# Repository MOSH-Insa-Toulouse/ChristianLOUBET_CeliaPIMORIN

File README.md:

# Projet_MOSH 

# 1. Introduction

Le 25 janvier 2021, nous avons commencé le projet «du capteur au banc de test en open source hardware», ce projet a pour but de vérifier la viabilité de la technologie des capteurs électronique à base de papier. Les capteurs à base papier peuvent être utilisé comme jauges de contrainte pour détecter les déformations: de compression et de traction. Ces capteurs peuvent être fabriqué sans électrodes métalliques en utilisant seulement le graphite issu des crayons à papier. Afin de tester nos capteurs nous avons réalisé notre banc de test et nous exploitons nos capteurs avec un circuit imprimé connecté à une Shield Arduino, ce montage transmet par Bluetooth nos mesures vers l’application APK, nous utilisons cette application sur nos smartphones. 

# 2. Capteur Graphite

La résistance du capteur graphite: Sur le papier est déposé du graphite, des atomes de carbones sont donc à la surface du papier, il y a une distance a entre chacun des atomes. Quand le capteur subit une déformation, sa longueur L s’agrandit/diminue et il en va de même pour la distance a entre les atomes. La déformation du capteur papier fait varier la résistance du capteur, car la longueur du capteur et la distance entre les atomes varie elle aussi. La sensibilité du capteur est très grande car elle dépend de l'effet tunnel qui dépend exponentiellement de la ditance entre le particules. Nos capteurs papier ont une zone nominale d’emploi, il ne faut pas trop déformer les capteurs(la déformation ne doit dépasser les 1 %).Les mines de crayon les plus dures(9H, 7H, 5H...) contiennent une proportion plus élevée de colle argileuse tandis que les mines les plus molles (5B,7B, 9B...) ont une proportion de particules de graphite, moins il y a de graphite sur le papier et plus la résistance du capteur augmente. 

Le principe physique du capteur repose sur les systèmes granulaires. Un système granulaire est un système avec des grains de tailles nanométrique où la conductance intragrain est très grande devant la conductance intergrain. En effet la conductance inter grain est la conductance entre deux particules et la conductance intragrain dépend de la diffusivité de la particule quantique qui depend de l'espacement entre les niveaux d'énergie. 
La conductance dans un système granulaire dépend de la constante de barrière tunnel, l'interdistance, l'energie de chargement et de la température.

# 3. Code Arduino
Quand nous connectons notre circuit imprimé avec le Shield Arduino, les pin Rx et Tx du circuit sont connectés aux ports 10 et 11 du Shield. En fait, les port 0 et 1 du Shield sont automatiquement reconfigurés : pin 0 et pin1 deviennent Rx et Tx, il devient donc impossible d’utiliser ces 2 ports, les port 10 et 11 sont donc redéfinies sur le code pour pouvoir transmettre les informations par le module HC-05.
Nous avons codé plusieurs fonctions sur Arduino, la première permet de transmettre par Bluetooth la valeur de la tension aux bornes du capteur papier, la tension est codée en binaire et envoyée par paquet de 10 bit, la seconde fonction affiche les valeurs de la tension (mesuré en Volt, il y a une conversion qui est faite dans le code) et la valeur de la résistance (en Ohm) sur l’écran OLED, Il faut noter que les mesures sont prises toutes les 20 millisecondes. 

# 4. Code APK
Sur ce code APK, nous avons organisé la face avant avec un canvas pour représenter graphiquement la résistance du capteur en temps réel, nous pouvons nous connecter par Bluetooth en sélectionnant les appareils détectables par le smartphone. Notre code traite les données envoyées par Bluetooth, il calcule la valeur de la résistance.

# 5. La Shield
Nous avons pu souder notre circuit imprimé sans court-circuit, nous avons soudé 4 ports femelles supplémentaires : 2 pour connecter les pinces qui sont reliées au capteur papier et 2 autres afin de changer plus facilement la résistance R2, cette résistance fait varier la valeur du gain d’amplification, notre Shield Arduino est alimentée sous 5 Volt, mais en fonction de la quantité de graphite déposée sur le capteur et de la valeur de R2, notre signal peut saturer à 5 Volt ou bien être tellement faible qu’il n’ai pas détectable. 
Enfin, nous avons des ports pour connecter l’écran OLED, l’encodeur rotatoire et le module Bluetooth.

Sur KiCad, nous avons créé des emplacements pour les connecteurs du module HC-05, de l’écran OLED, de l’encodeur rotatoire, de l’amplificateur et le capteur papier. Sur la schématique, nous avons dessiné le montage transimpédance (Filtre passe-bas + montage amplificateur)
Nous avons routé les différents emplacements entre eux, toutes les masses sont reliée par un plan de masse. 

# 6. Le Protocol pour le banc de test

Au début nous déformions notre capteur avec un banc de test cylindrique mais nous avions des mesures aberrantes, c’est en montrant nos résultats à notre professeur que nous avons compris l’origine du problème: les rayons de courbure du cylindre sont trop grands et cela fait dépasser la zone nominale d’emploi de nos capteurs. Sur conseil de Monsieur Grisolia, nous avons utilisé un autre banc de test: avec du ruban adhésif, nous fixons les pinces du capteur sur le bord d’une table, nous mettions une règle sous l’extrémité du capteur qui dépasse de la table. Avec la règle nous déformions le capteur, nous la faisions glisser très légèrement vers le haut. Cela permet de mieux contrôler la déformation du capteur.

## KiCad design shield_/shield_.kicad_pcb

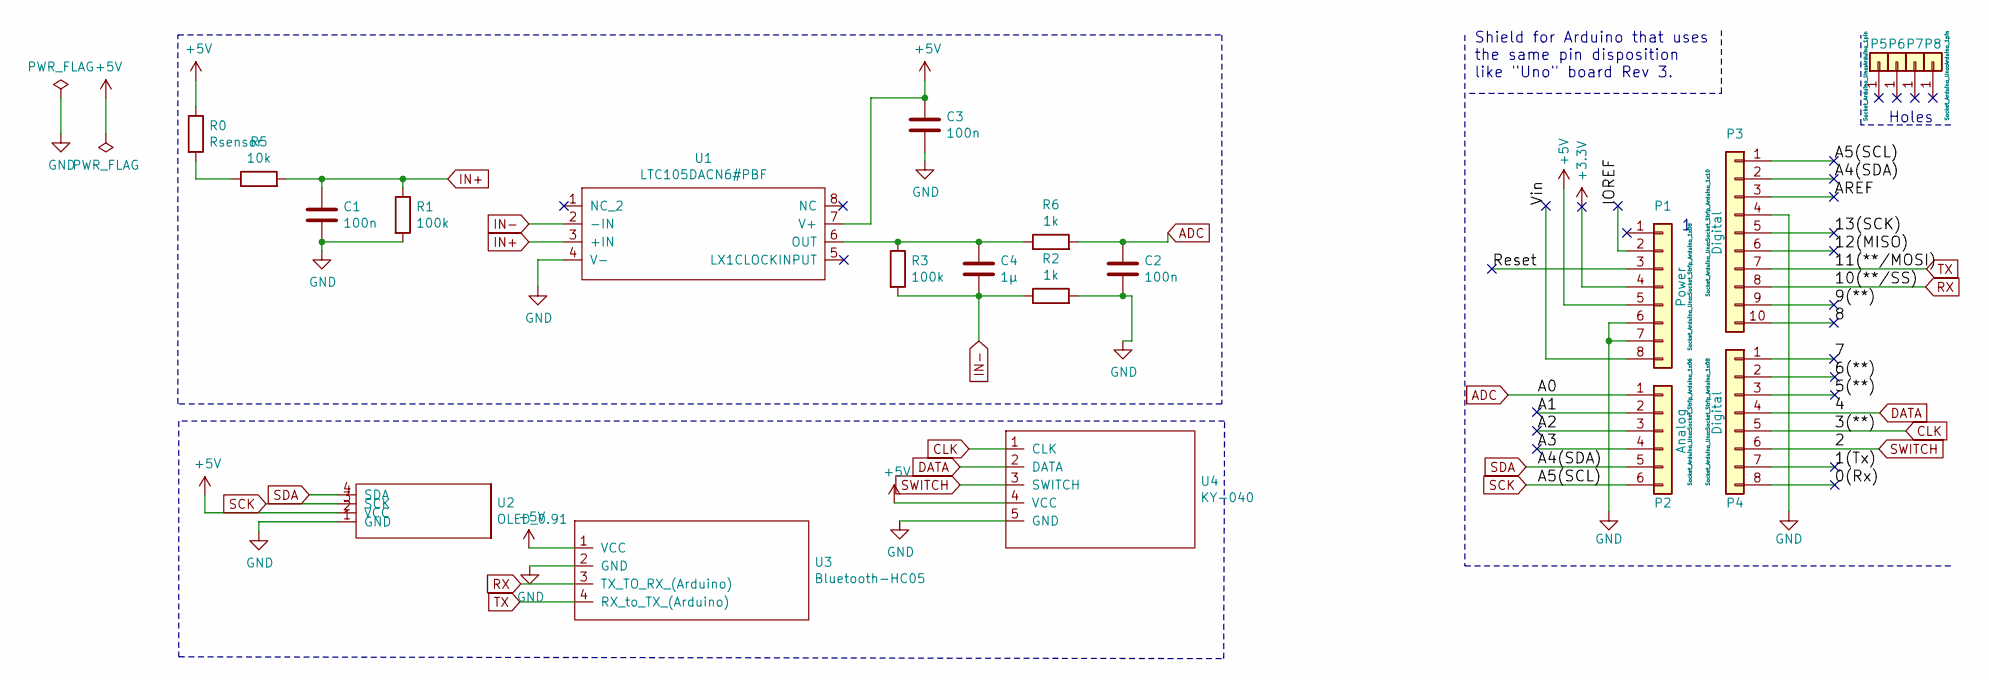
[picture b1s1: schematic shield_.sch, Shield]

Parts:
C1, C2, C3: 100n; C_Axial_L5.1mm_D3.1mm_P7.50mm_Horizontal
C4: 1µ; C_Axial_L5.1mm_D3.1mm_P7.50mm_Horizontal
P1: Power; Socket_Strip_Arduino_1x08
P2: Analog; Socket_Strip_Arduino_1x06
P3: Digital; Socket_Strip_Arduino_1x10
P4: Digital; Socket_Strip_Arduino_1x08
P5, P6, P7, P8: CONN_01X01; Arduino_1pin
R0: Rsensor; R_Axial_DIN0207_L6.3mm_D2.5mm_P10.16mm_Horizontal
R1, R3: 100k; R_Axial_DIN0207_L6.3mm_D2.5mm_P10.16mm_Horizontal
R2, R6: 1k; R_Axial_DIN0207_L6.3mm_D2.5mm_P10.16mm_Horizontal
R5: 10k; R_Axial_DIN0207_L6.3mm_D2.5mm_P10.16mm_Horizontal
U1: LTC105DACN6#PBF; amplificateur
U2: OLED_0.91; ECRAN_OLED
U3: Bluetooth-HC05; SIP-4bluetooth
U4: KY-040; SIP-6

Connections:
+3V3: P1.4
+5V: C3.1, P1.5, R0.1, U1.7 (V+), U2.2 (VCC), U3.1 (VCC), U4.4 (VCC)
/0(Rx): P4.8
/1(Tx): P4.7
/5(**): P4.3
/6(**): P4.2
/7: P4.1
/8: P3.10
/9(**): P3.9
/12(MISO): P3.6
/13(SCK): P3.5
/A1: P2.2
/A2: P2.3
/A3: P2.4
/AREF: P3.3
/IOREF: P1.2
/Reset: P1.3
/Vin: P1.8
ADC: C2.1, P2.1, R6.2
CLK: P4.5, U4.1 (CLK)
DATA: P4.4, U4.2 (DATA)
GND: C1.2, C2.2, C3.2, P1.6, P1.7, P3.4, R1.2, R2.2, U1.4 (V-), U2.1 (GND), U3.2 (GND), U4.5 (GND)
IN+: C1.1, R1.1, R5.2, U1.3 (+IN)
IN-: C4.2, R2.1, R3.2, U1.2 (-IN)
unnamed: C4.1, R3.1, R6.1, U1.6 (OUT)
unnamed: R0.2, R5.1
RX: P3.8, U3.3 (TX_TO_RX_(Arduino))
SCK: P2.6, P3.1, U2.3 (SCK)
SDA: P2.5, P3.2, U2.4 (SDA)
SWITCH: P4.6, U4.3 (SWITCH)
TX: P3.7, U3.4 (RX_to_TX_(Arduino))

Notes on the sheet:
Holes
Shield for Arduino that uses the same pin disposition like "Uno" board Rev 3.

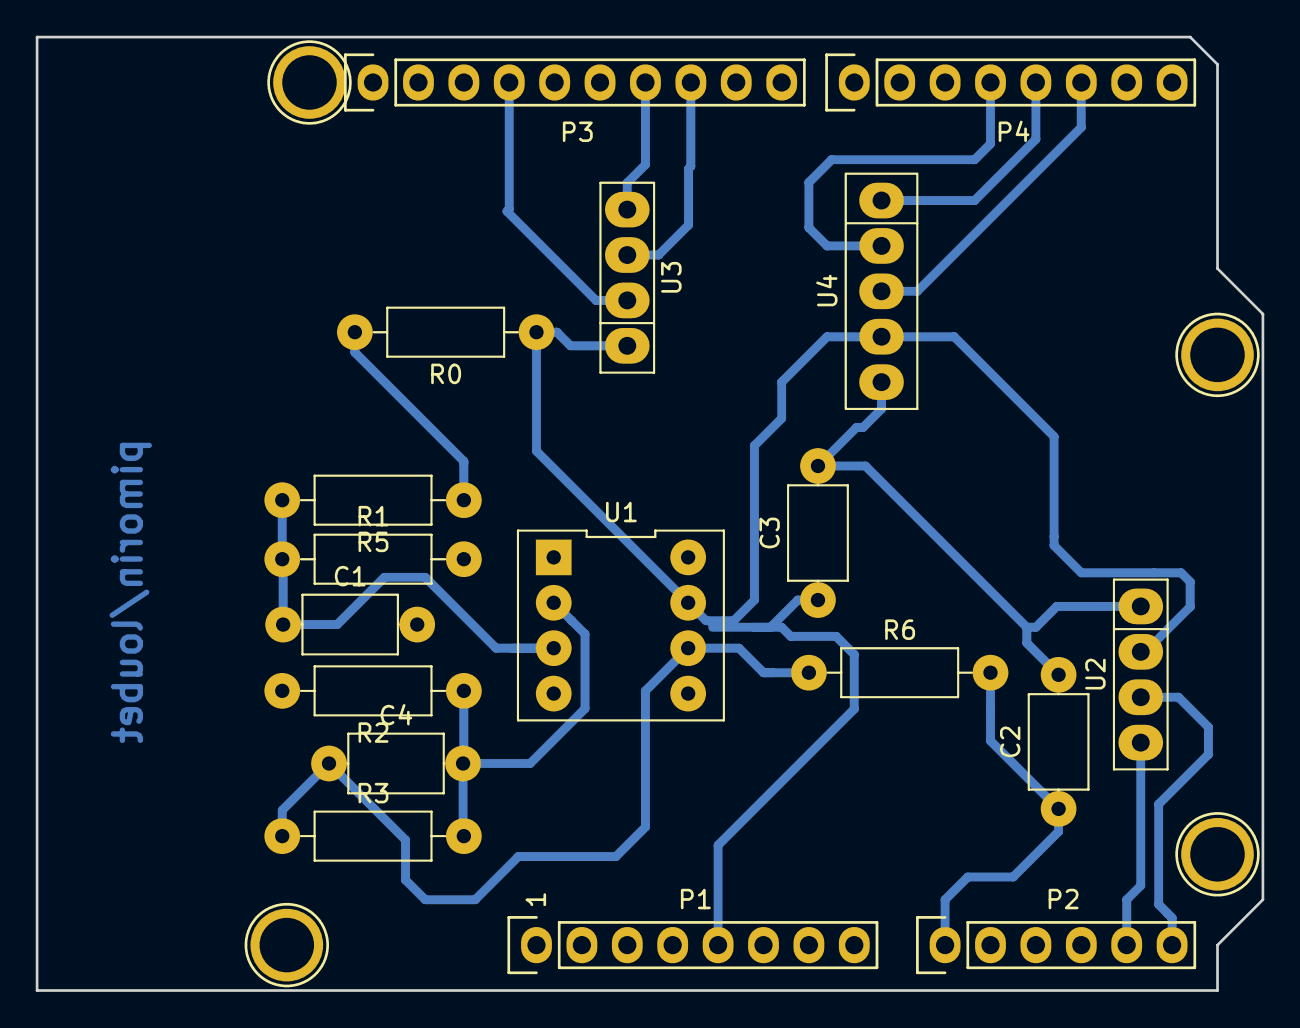
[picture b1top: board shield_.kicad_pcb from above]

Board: 2 copper layers, 68.6 x 53.3 mm, 22 parts (0 on the bottom side), 14 nets.

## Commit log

2021-05-02 Update README.md
    début du read me
2021-05-02 Import Publication sur les capteurs de graphite
2021-05-02 import datasheet 2
2021-05-02 Import Excel pour les mesures sur le capteur avec les mesures en fonction du temps
2021-05-02 explications capteur schéma
2021-05-02 import photo aplication pour readme
2021-05-04 import prgrm arduino
2021-05-04 Code APK
2021-05-04 images du montage et de l'appli
2021-05-05 Excel pour les mesures
2021-05-05 Datasheet
